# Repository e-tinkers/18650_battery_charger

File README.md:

## What this about
This repository contains the design files for my 18650 and single cell Li-Po charger which also consists of load-shring circuitry, and a buck/boost converter (3.3V/5.0V, 500mA output) with very low quiescent current (20uA).

## The motivation
All the 18650 battery chargers that can be found from AliExpress have serious design faults, and the 18650 battery is safer to be used with the protection circuit permanently attached to it. With the modification added to 18650, the commercial available battery holders for 18650 no longer fit. So I decided to design my own charger with custom 18650 battery holder to fit the modified battery, and add a low quiescent current buck/boost converter with 3.3V/5V output that I can used for my electronic projects.

## The design goals
1. On-board 18650 battery holder able to fit standard 18650 and modified one;
2. USB Type C power input port;
3. Capable to charge either 18650 battery and Li-Po battery (via JST connector);
4. Battery Protection for standard 18650 battery;
5. Load-sharing circuitry so it can power the load while charging;
6. Boost/Buck converter capable to deliver 500mA power with either 3.3V or 5V output;
7. Low quiescent current for IoT application.

Read more in details about the design considerations from my [blog post](https://www.e-tinkers.com/2025/08/design-my-own-tp4056-li-ion-charger-and-iot-power-supply-subsystem/).

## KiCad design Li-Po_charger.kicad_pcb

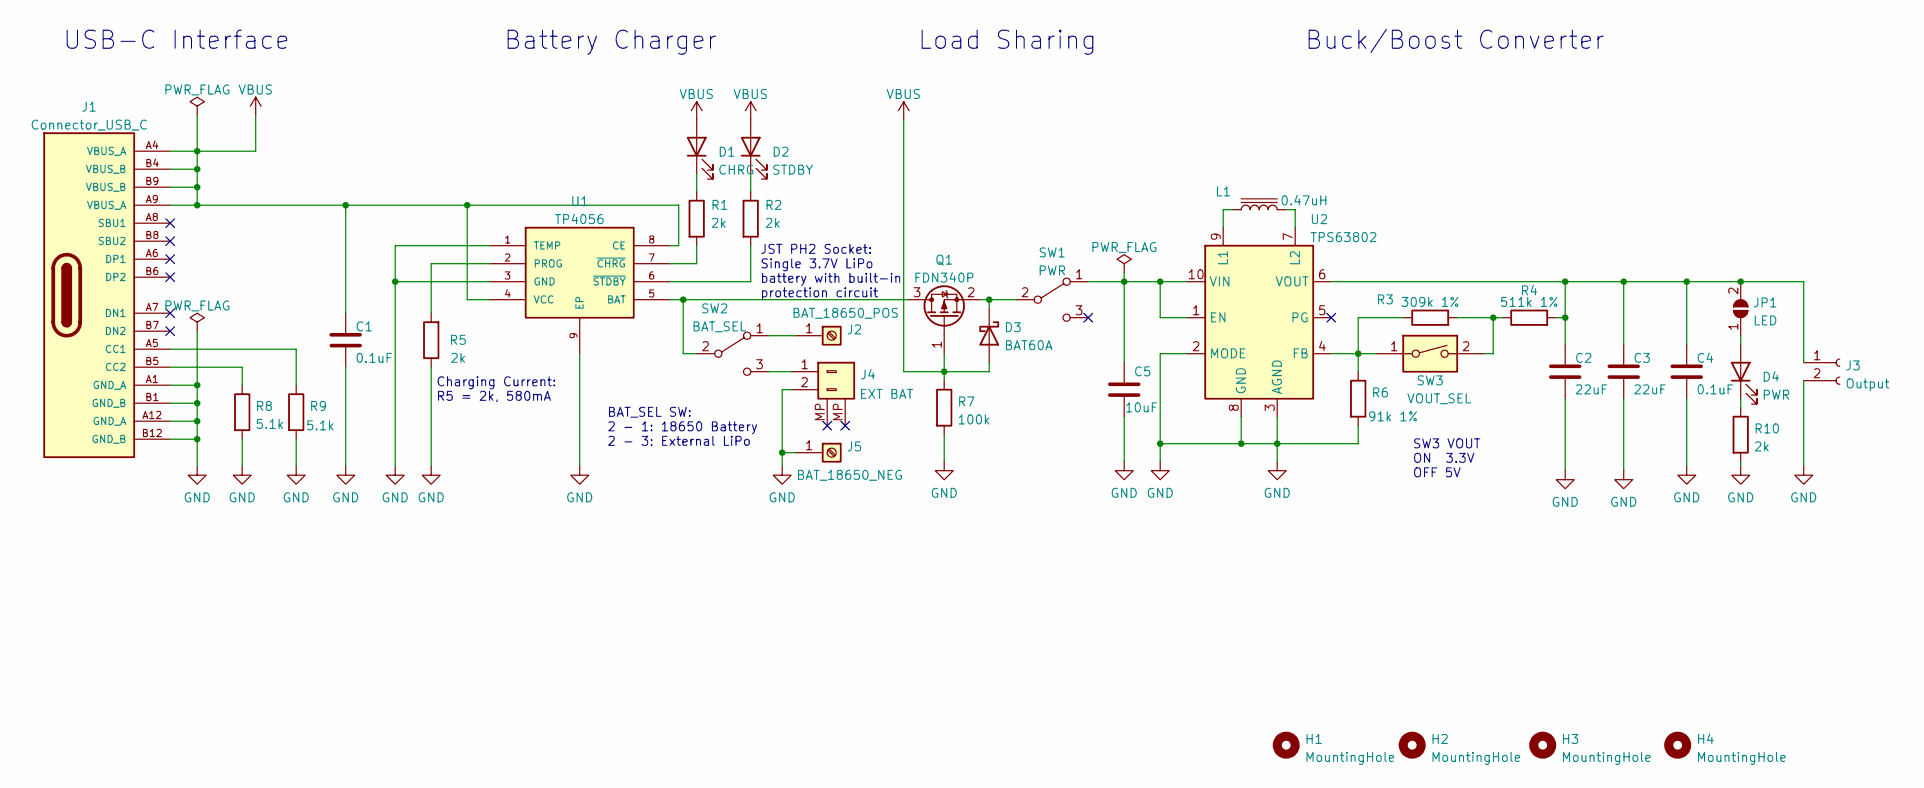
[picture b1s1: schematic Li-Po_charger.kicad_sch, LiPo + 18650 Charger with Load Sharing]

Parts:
C1, C4: 0.1uF; C_0603_1608Metric
C2, C3: 22uF; C_0603_1608Metric
C5: 10uF; C_0603_1608Metric
D1: CHRG; LED_0603_1608Metric
D2: STDBY; LED_0603_1608Metric
D3: BAT60A; D_SOD-323_HandSoldering
D4: PWR; LED_0603_1608Metric
H1, H2, H3, H4: MountingHole; MountingHole_2.7mm_M2.5
J1: Connector_USB_C; XUNPU_TYPEC-304-ACP16
J2: BAT_18650_POS; BAT-SMD_MY-18650-02
J3: Output; PinSocket_1x02_P2.54mm_Vertical
J4: EXT BAT; JST_PH_S2B-PH-SM4-TB_1x02-1MP_P2.00mm_Horizontal
J5: BAT_18650_NEG; BAT-SMD_MY-18650-02
JP1: LED; SolderJumper-2_P1.3mm_Open_RoundedPad1.0x1.5mm
L1: 0.47uH; L_Taiyo-Yuden_NR-50xx_HandSoldering
Q1: FDN340P; SOT-23_Handsoldering
R1, R2, R5, R10: 2k; R_0603_1608Metric
R3: 309k 1%; R_0603_1608Metric
R4: 511k 1%; R_0603_1608Metric
R6: 91k 1%; R_0603_1608Metric
R7: 100k; R_0603_1608Metric
R8, R9: 5.1k; R_0603_1608Metric
SW1: PWR; SW_SPDT_MK-12C02-C963206
SW2: BAT_SEL; SW_SPDT_MK-12C02-C963206
SW3: VOUT_SEL; SW_DIP_SPSTx01_Slide_Copal_CHS-01A_W5.08mm_P1.27mm_JPin
U1: TP4056; SOP127P600X175-9N
U2: TPS63802; TPS63802DLAR

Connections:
GND: C1.2, C2.2, C3.2, C4.2, C5.2, J1.A1 (GND_A), J1.A12 (GND_A), J1.B1 (GND_B), J1.B12 (GND_B), J3.2, J4.2, J5.1, R5.1, R6.2, R7.2, R8.2, R9.2, R10.2, U1.1 (TEMP), U1.3 (GND), U1.9 (EP), U2.2 (MODE), U2.3 (AGND), U2.8 (GND)
unnamed: C2.1, C3.1, C4.1, J3.1, JP1.2 (B), R4.2, U2.6 (VOUT)
unnamed: C5.1, SW1.1 (A), U2.1 (EN), U2.10 (VIN)
unnamed: D1.1 (K), R1.1
unnamed: D2.1 (K), R2.1
unnamed: D3.1 (K), Q1.2 (S), SW1.2 (B)
unnamed: D4.1 (K), R10.1
unnamed: D4.2 (A), JP1.1 (A)
unnamed: J1.A5 (CC1), R9.1
unnamed: J1.B5 (CC2), R8.1
unnamed: J2.1, SW2.1 (A)
unnamed: J4.1, SW2.3 (C)
unnamed: L1.1, U2.9 (L1)
unnamed: L1.2, U2.7 (L2)
unnamed: Q1.3 (D), SW2.2 (B), U1.5 (BAT)
unnamed: R1.2, U1.7 (~CHRG)
unnamed: R2.2, U1.6 (~STDBY)
unnamed: R3.1, R6.1, SW3.1, U2.4 (FB)
unnamed: R3.2, R4.1, SW3.2
unnamed: R5.2, U1.2 (PROG)
VBUS: C1.1, D1.2 (A), D2.2 (A), D3.2 (A), J1.A4 (VBUS_A), J1.A9 (VBUS_A), J1.B4 (VBUS_B), J1.B9 (VBUS_B), Q1.1 (G), R7.1, U1.4 (VCC), U1.8 (CE)

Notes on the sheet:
Battery Charger
Charging Current: R5 = 2k, 580mA
BAT_SEL SW: 2 - 1: 18650 Battery 2 - 3: External LiPo
Buck/Boost Converter
SW3 VOUT ON 3.3V OFF 5V
USB-C Interface
Load Sharing
JST PH2 Socket: Single 3.7V LiPo battery with built-in protection circuit

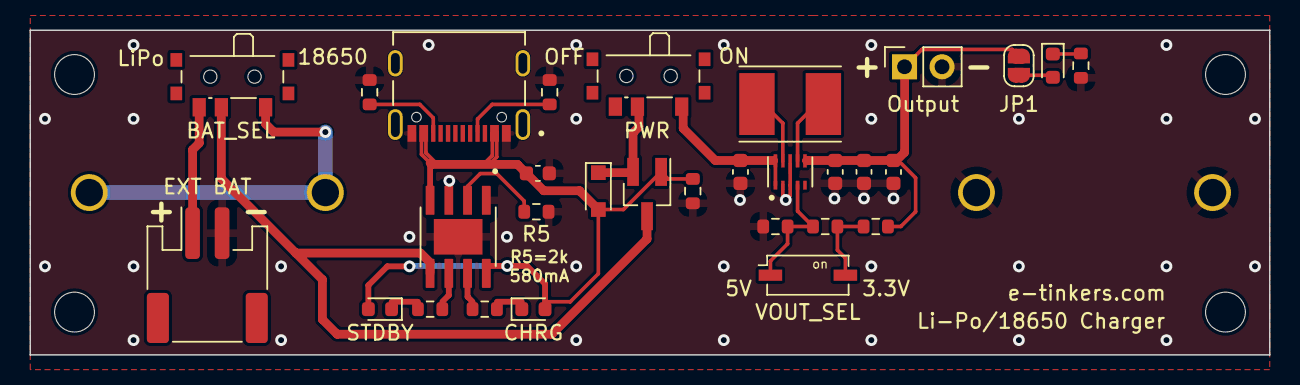
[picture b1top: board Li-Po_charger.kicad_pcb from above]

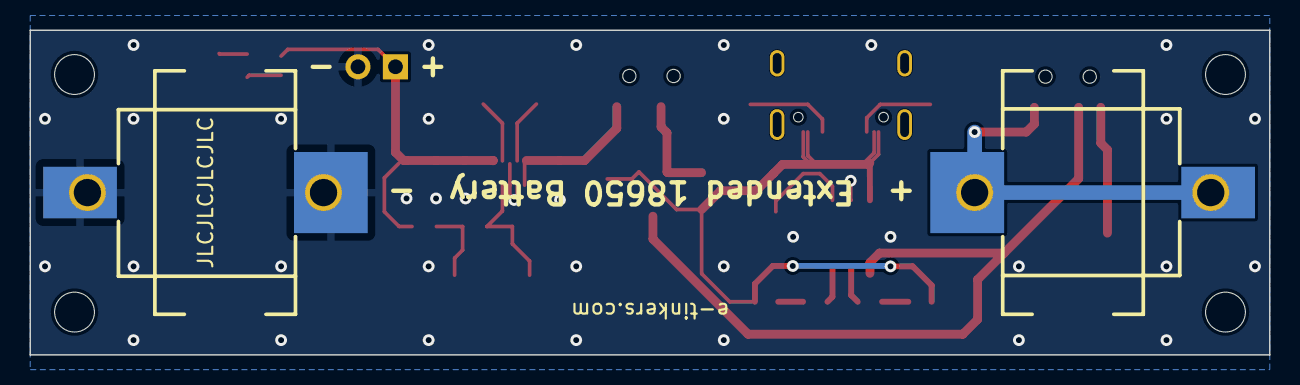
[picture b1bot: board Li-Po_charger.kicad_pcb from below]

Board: 2 copper layers, 84.0 x 22.0 mm, 36 parts (2 on the bottom side), 21 nets.

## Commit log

2025-09-14 upload to git
